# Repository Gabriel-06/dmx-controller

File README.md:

# DMX Controller
## The Boards 
### Board 2 Revision A
In revision A (REV A) the `S̅R̅C̅L̅R̅` pin on the shift register is pulled HIGH, this keeps the shift registers in a constantly cleared state. I thought that the issue was with the output enable pin (`O̅E̅`) as I said in my AT2, but this wasn’t the issue. I’m not even sure where that came from as the correction that I made to my board was on the right pin (`S̅R̅C̅L̅R̅`). In REV A, the NPN transistors to properly drive the 7-segment display are also missing. In order to use this revision, 2 cuts must be made as shown to cut the `S̅R̅C̅L̅R̅` pin from the ground plane. A wire can then be soldered directly onto the pin of the shift register that goes to an exposed +5V source. 2 possibilities for this are shown on the image below. In this revision the ICSP header is also flipped so the connector pinout is only correct on the back of the board, even though the silkscreen shows that the connector should be on the front. This is fixed in later revisions (I think). In this revision, for it to be bus powered (powered from USB) a wire needs to be soldered in from the fuse of the USB to the +5V port on the other side of the board (also in the image below, the white wire). Solder to the side after the fuse, as then it still gives you the protection. 

### Board 2 Revision B
In revision B (REV B), the same mistake exists regarding the `S̅R̅C̅L̅R̅` pin, except this time the output enable pin is wrongly pulled HIGH as well. 1 step forward, 2 steps back. So, for the revision B board, 3 points need to be cut, as outlined in the image below. Cut 1 is to cut the +5V rail going to the `O̅E̅` pin on the shift register. Cuts 2 and 3 are both to cut the `S̅R̅C̅L̅R̅` pin from the ground plane. This cut leaves you with a small floating ground plane island, but it shouldn’t really matter, there isn’t anything that sensitive around it. For all 3 cuts, you can simply use a small X-Acto knife or Stanley knife to cut the trace, similar to how you might on a strip board. 2 wires then have to be soldered directly onto the pins of the shift register going to an exposed +5V and GND point. I recommend using the exposed power input/output, as that isn’t used at all in the current design.

### Board 2 Revision C
Revision C (REV C) should have hopefully fixed all the issues, although I’m not going to order them, I’m happy just to keep the wires there. The files for it are in the GitHub if you would like to produce your own batch. No guarantees though….

### Board 1 Revision A
Similar to board 2, in revision A (REV A) of this board, the `S̅R̅C̅L̅R̅` pin on the shift registers are pulled HIGH, this keeps the shift registers in a constantly cleared state. 2 cuts need to make in the positions shown on the image below. A wire then has to be soldered directly onto the pin of the shift register and connected to a +5V source. The most convenient for me was the interconnect’s +5V line, as shown in the image below. 

### Board 1 Revision B
Revision B (REV B) should hopefully have fixed the issue. I’m not going to order any boards of this revision, but the files for it are in the GitHub, if you need to order anymore, or need it for reference.

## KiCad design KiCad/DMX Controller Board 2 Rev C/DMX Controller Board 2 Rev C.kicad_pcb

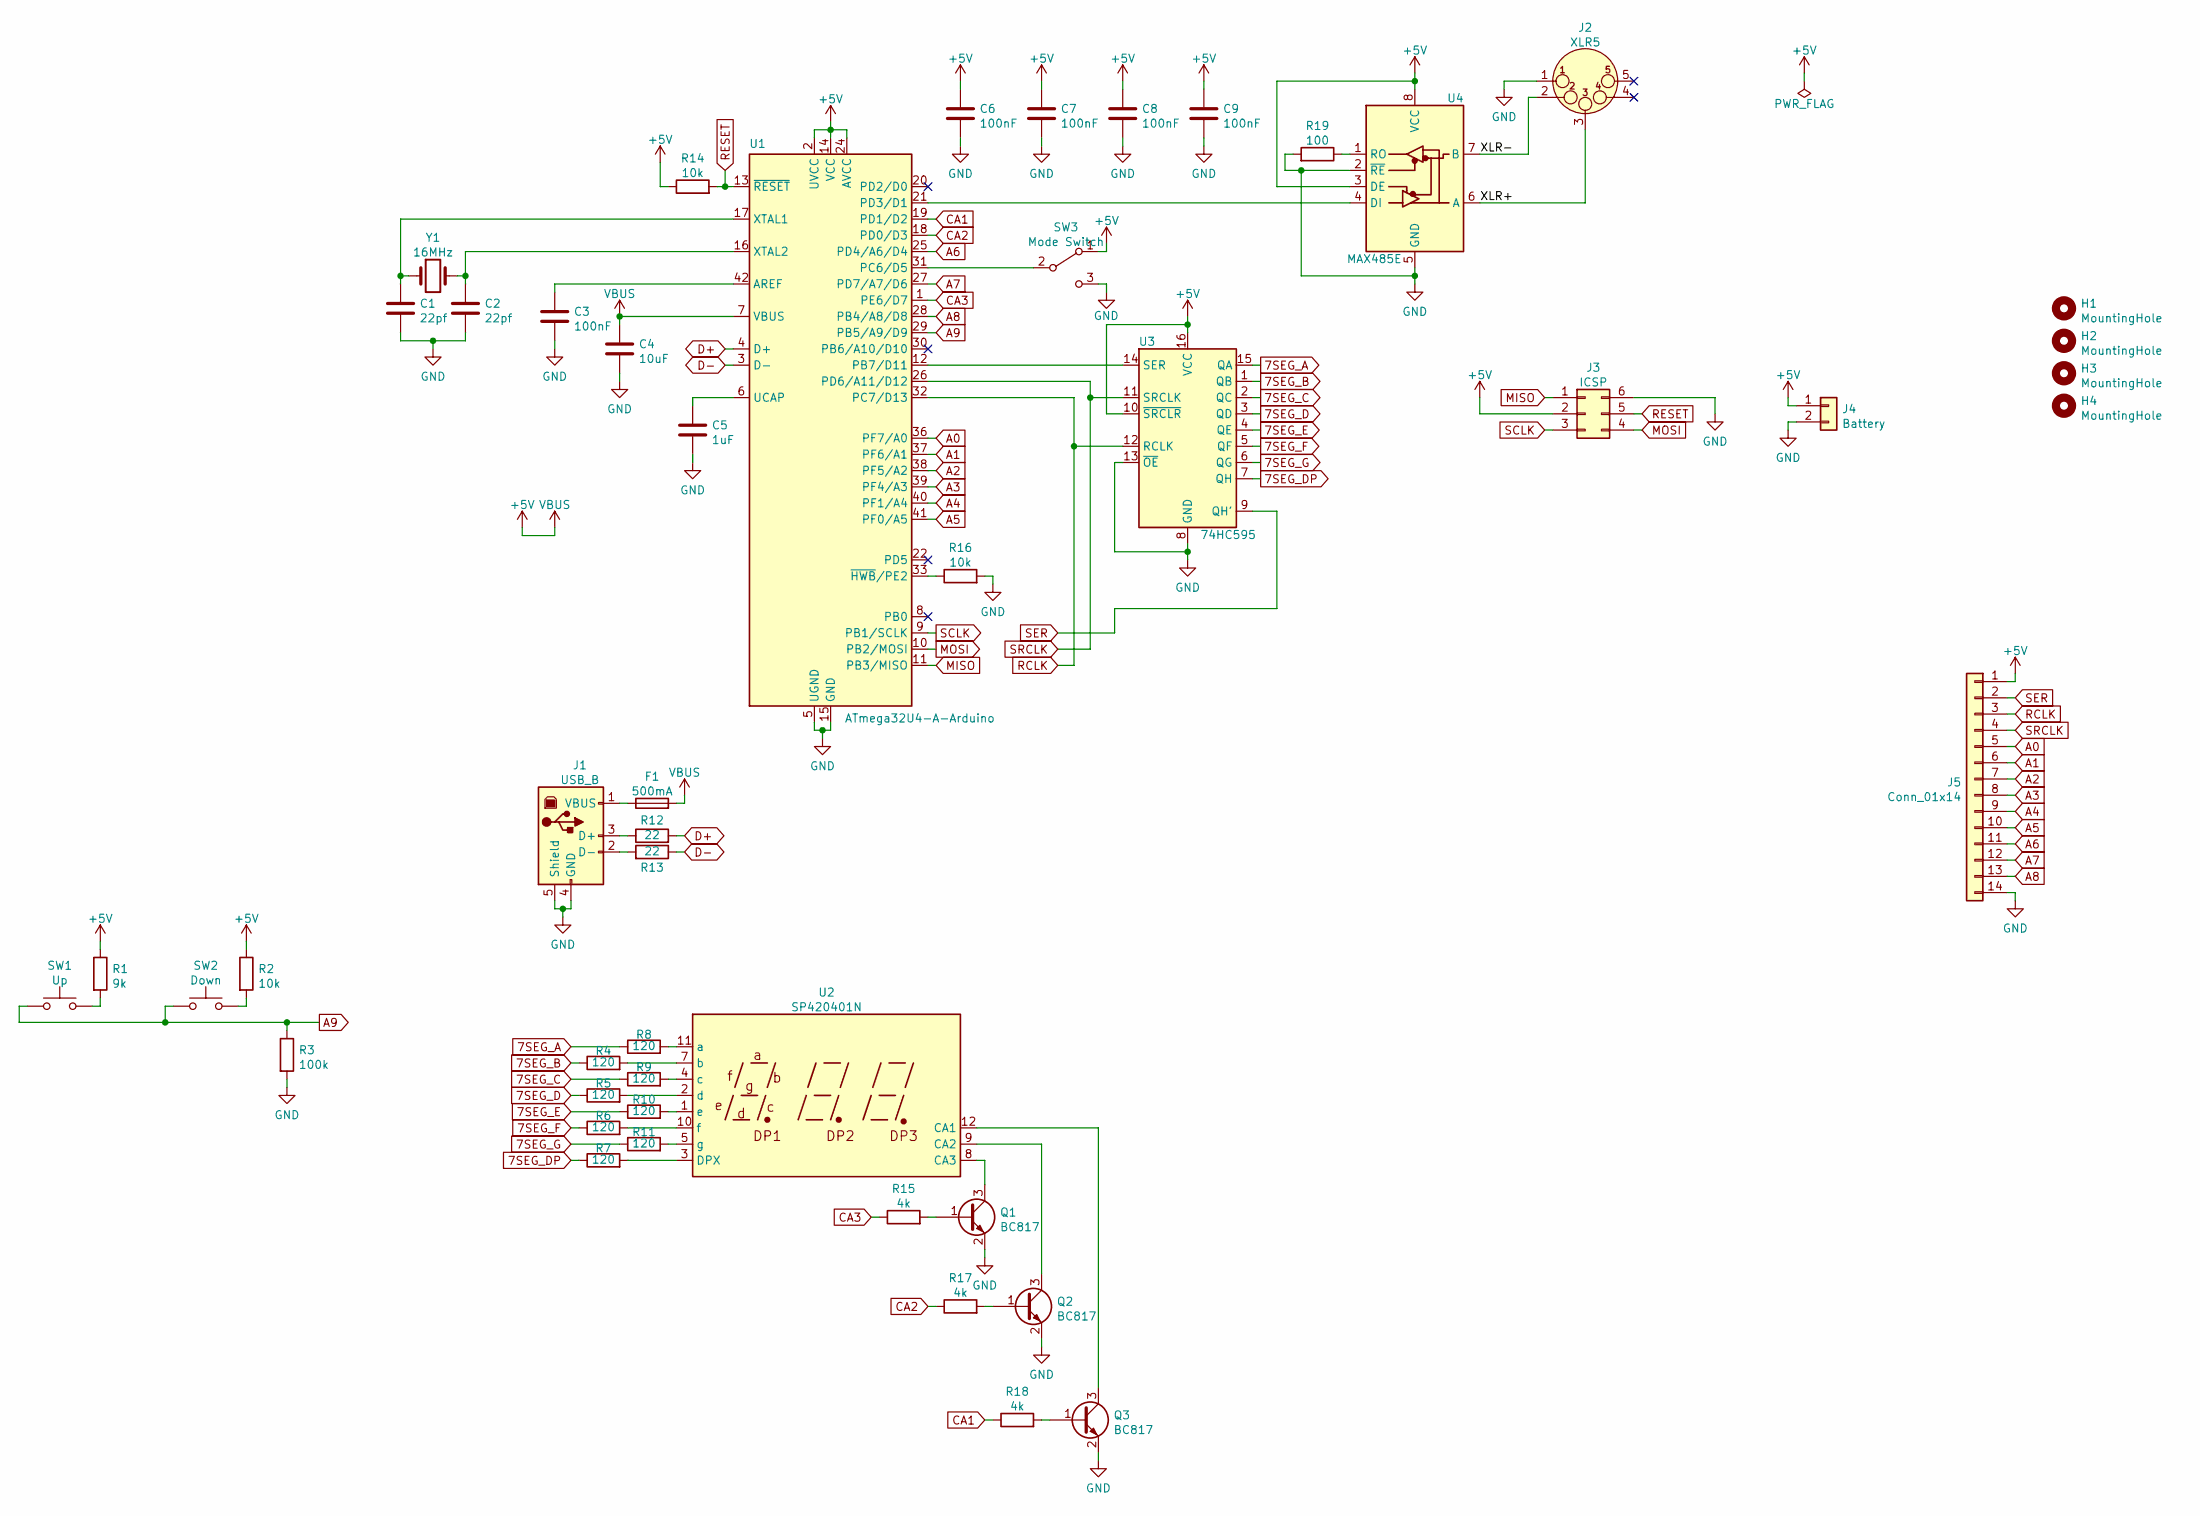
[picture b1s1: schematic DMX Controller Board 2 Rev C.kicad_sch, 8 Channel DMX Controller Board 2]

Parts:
C1, C2: 22pf; C_0805_2012Metric_Pad1.18x1.45mm_HandSolder
C3, C6, C7, C8, C9: 100nF; C_0805_2012Metric_Pad1.18x1.45mm_HandSolder
C4: 10uF; C_0805_2012Metric_Pad1.18x1.45mm_HandSolder
C5: 1uF; C_0805_2012Metric_Pad1.18x1.45mm_HandSolder
F1: 500mA; Fuse_1206_3216Metric_Pad1.42x1.75mm_HandSolder
H1, H2, H3, H4: MountingHole; MountingHole_3.2mm_M3
J1: USB_B; USB_B_USB-B02
J2: XLR5; PinHeader_1x03_P2.54mm_Vertical
J3: ICSP; PinSocket_2x03_P2.54mm_Vertical
J4: Battery; PinSocket_1x02_P2.54mm_Vertical
J5: Conn_01x14; PinSocket_1x14_P2.54mm_Vertical
Q1, Q2, Q3: BC817; SOT-23
R1: 9k; R_0805_2012Metric_Pad1.20x1.40mm_HandSolder
R2, R14, R16: 10k; R_0805_2012Metric_Pad1.20x1.40mm_HandSolder
R3: 100k; R_0805_2012Metric_Pad1.20x1.40mm_HandSolder
R4, R5, R6, R7, R8, R9, R10, R11: 120; R_0805_2012Metric_Pad1.20x1.40mm_HandSolder
R12, R13: 22; R_0805_2012Metric_Pad1.20x1.40mm_HandSolder
R15, R17, R18: 4k; R_0805_2012Metric_Pad1.20x1.40mm_HandSolder
R19: 100; R_0805_2012Metric_Pad1.20x1.40mm_HandSolder
SW1: Up; SW_PUSH_6mm_H13mm
SW2: Down; SW_PUSH_6mm_H13mm
SW3: Mode Switch; PinHeader_1x03_P2.54mm_Vertical
U1: ATmega32U4-A-Arduino; TQFP-44_10x10mm_P0.8mm
U2: SP420401N
U3: 74HC595; SOP-16_3.9x9.9mm_P1.27mm
U4: MAX485E; SOP-8_3.9x4.9mm_P1.27mm
Y1: 16MHz; Crystal_HC49-4H_Vertical

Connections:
7SEG_A: R8.1, U3.15 (QA)
7SEG_B: R4.1, U3.1 (QB)
7SEG_C: R9.1, U3.2 (QC)
7SEG_D: R5.1, U3.3 (QD)
7SEG_DP: R7.1, U3.7 (QH)
7SEG_E: R10.1, U3.4 (QE)
7SEG_F: R6.1, U3.5 (QF)
7SEG_G: R11.1, U3.6 (QG)
+5V: C4.1, C6.1, C7.1, C8.1, C9.1, F1.2, J3.2, J4.1, J5.1, R1.1, R2.1, R14.1, SW3.1 (A), U1.2 (UVCC), U1.7 (VBUS), U1.14 (VCC), U1.24 (AVCC), U1.34 (VCC), U1.44 (AVCC), U3.10 (~SRCLR), U3.16 (VCC), U4.3 (DE), U4.8 (VCC)
/XLR+: J2.3, U4.6 (A)
/XLR-: J2.2, U4.7 (B)
A0: J5.5, U1.36 (PF7/A0)
A1: J5.6, U1.37 (PF6/A1)
A2: J5.7, U1.38 (PF5/A2)
A3: J5.8, U1.39 (PF4/A3)
A4: J5.9, U1.40 (PF1/A4)
A5: J5.10, U1.41 (PF0/A5)
A6: J5.11, U1.25 (PD4/A6/D4)
A7: J5.12, U1.27 (PD7/A7/D6)
A8: J5.13, U1.28 (PB4/A8/D8)
A9: R3.1, SW1.1, SW2.1, U1.29 (PB5/A9/D9)
CA1: R18.1, U1.19 (PD1/D2)
CA2: R17.1, U1.18 (PD0/D3)
CA3: R15.1, U1.1 (PE6/D7)
D+: R12.2, U1.4 (D+)
D-: R13.1, U1.3 (D-)
GND: C1.2, C2.2, C3.2, C4.2, C5.2, C6.2, C7.2, C8.2, C9.2, J1.4 (GND), J1.5 (Shield), J2.1, J3.6, J4.2, J5.14, Q1.2 (E), Q2.2 (E), Q3.2 (E), R3.2, R16.2, R19.2, SW3.3 (C), U1.5 (UGND), U1.15 (GND), U1.23 (GND), U1.35 (GND), U1.43 (GND), U3.8 (GND), U3.13 (~OE), U4.2 (~RE), U4.5 (GND)
MISO: J3.1, U1.11 (PB3/MISO)
MOSI: J3.4, U1.10 (PB2/MOSI)
unnamed: C1.1, U1.17 (XTAL1), Y1.1
unnamed: C2.1, U1.16 (XTAL2), Y1.2
unnamed: C3.1, U1.42 (AREF)
unnamed: C5.1, U1.6 (UCAP)
unnamed: F1.1, J1.1 (VBUS)
unnamed: J1.2 (D-), R13.2
unnamed: J1.3 (D+), R12.1
unnamed: Q1.1 (B), R15.2
unnamed: Q1.3 (C), U2.8 (CA3)
unnamed: Q2.1 (B), R17.2
unnamed: Q2.3 (C), U2.9 (CA2)
unnamed: Q3.1 (B), R18.2
unnamed: Q3.3 (C), U2.12 (CA1)
unnamed: R1.2, SW1.2
unnamed: R2.2, SW2.2
unnamed: R4.2, U2.7 (b)
unnamed: R5.2, U2.2 (d)
unnamed: R6.2, U2.10 (f)
unnamed: R7.2, U2.3 (DPX)
unnamed: R8.2, U2.11 (a)
unnamed: R9.2, U2.4 (c)
unnamed: R10.2, U2.1 (e)
unnamed: R11.2, U2.5 (g)
unnamed: R16.1, U1.33 (~HWB~/PE2)
unnamed: R19.1, U4.1 (RO)
unnamed: SW3.2 (B), U1.31 (PC6/D5)
unnamed: U1.12 (PB7/D11), U3.14 (SER)
unnamed: U1.21 (PD3/D1), U4.4 (DI)
RCLK: J5.3, U1.32 (PC7/D13), U3.12 (RCLK)
RESET: J3.5, R14.2, U1.13 (~RESET)
SCLK: J3.3, U1.9 (PB1/SCLK)
SER: J5.2, U3.9 (QH')
SRCLK: J5.4, U1.26 (PD6/A11/D12), U3.11 (SRCLK)

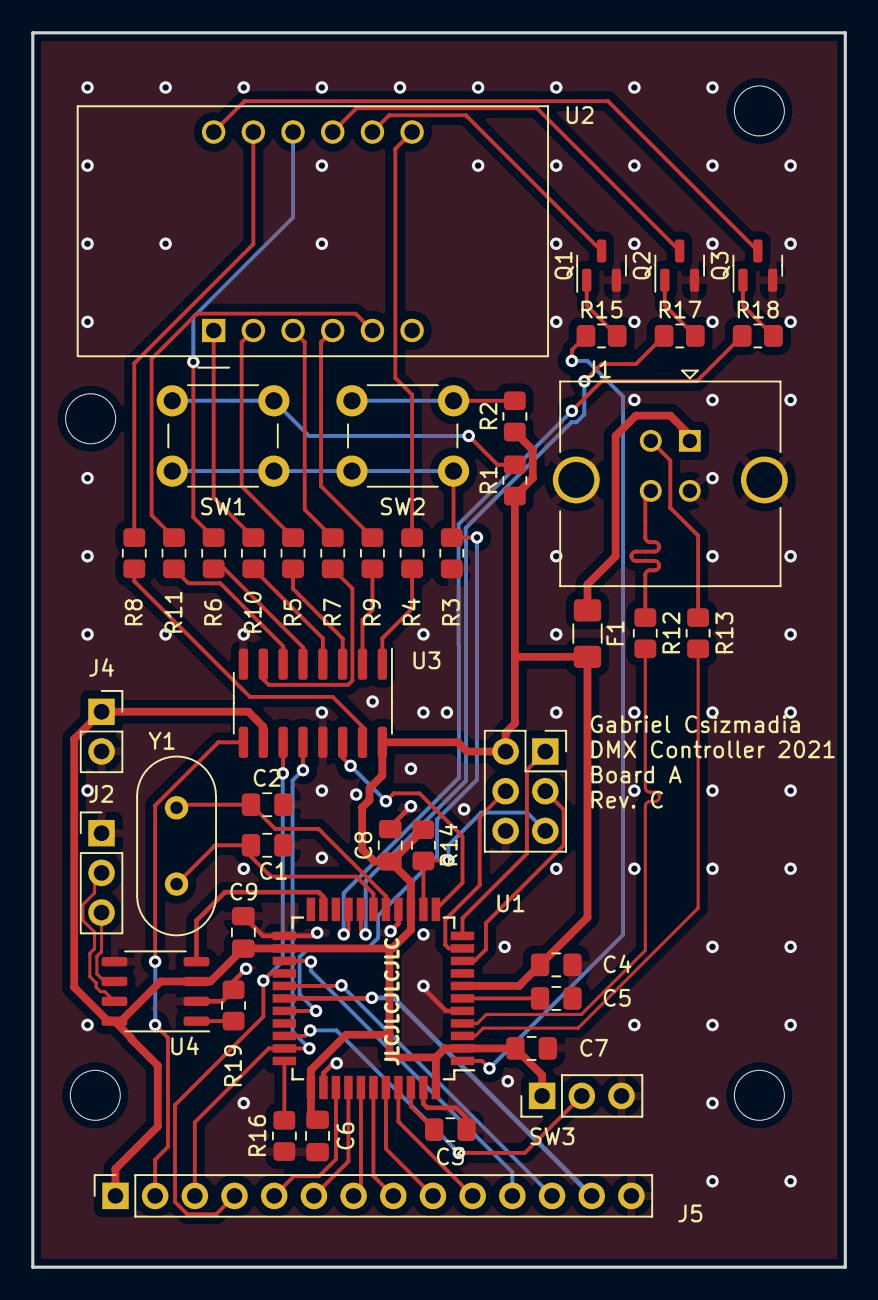
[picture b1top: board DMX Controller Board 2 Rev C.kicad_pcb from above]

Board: 2 copper layers, 52.0 x 79.0 mm, 49 parts (0 on the bottom side), 62 nets.

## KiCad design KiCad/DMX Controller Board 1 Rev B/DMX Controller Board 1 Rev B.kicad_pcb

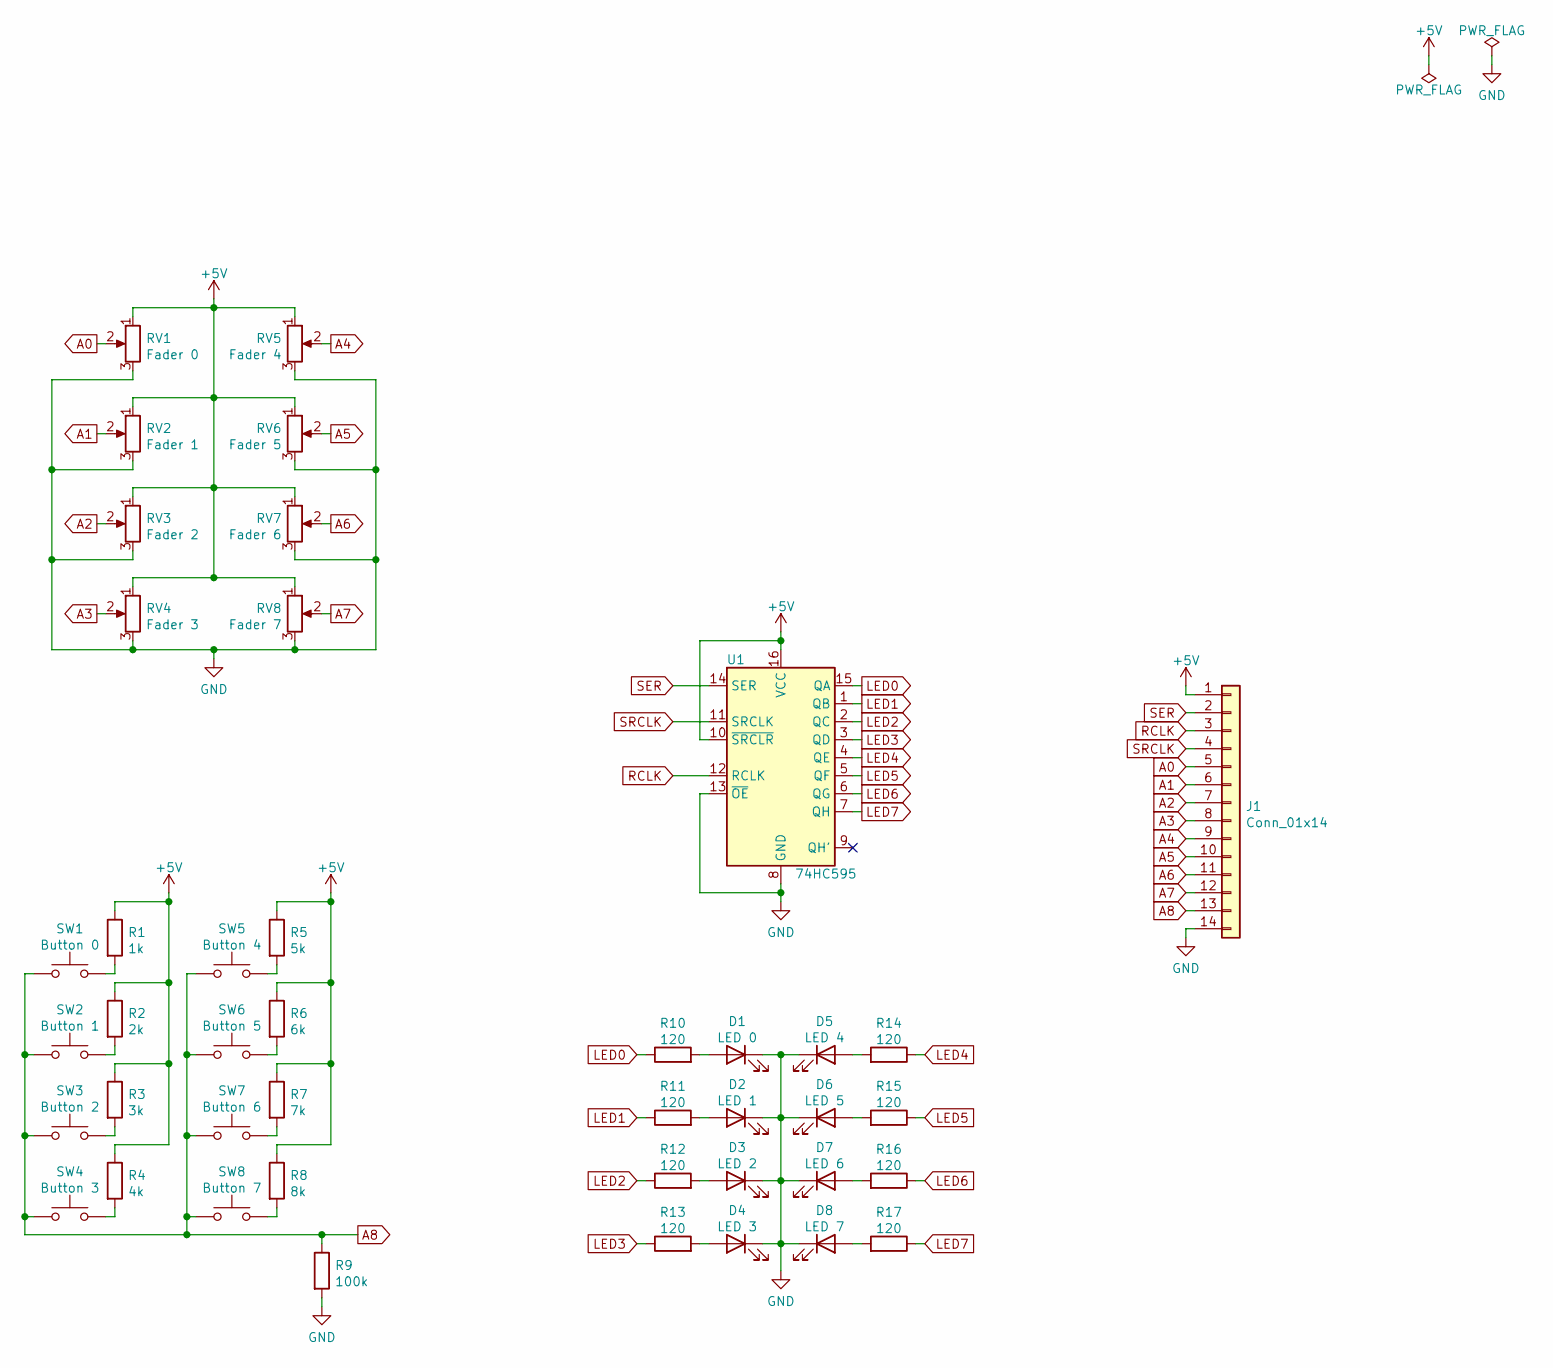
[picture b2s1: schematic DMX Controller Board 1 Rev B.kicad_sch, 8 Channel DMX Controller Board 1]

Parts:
D1: LED 0; LED_D3.0mm
D2: LED 1; LED_D3.0mm
D3: LED 2; LED_D3.0mm
D4: LED 3; LED_D3.0mm
D5: LED 4; LED_D3.0mm
D6: LED 5; LED_D3.0mm
D7: LED 6; LED_D3.0mm
D8: LED 7; LED_D3.0mm
J1: Conn_01x14; PinSocket_1x14_P2.54mm_Vertical
R1: 1k; R_0805_2012Metric_Pad1.20x1.40mm_HandSolder
R2: 2k; R_0805_2012Metric_Pad1.20x1.40mm_HandSolder
R3: 3k; R_0805_2012Metric_Pad1.20x1.40mm_HandSolder
R4: 4k; R_0805_2012Metric_Pad1.20x1.40mm_HandSolder
R5: 5k; R_0805_2012Metric_Pad1.20x1.40mm_HandSolder
R6: 6k; R_0805_2012Metric_Pad1.20x1.40mm_HandSolder
R7: 7k; R_0805_2012Metric_Pad1.20x1.40mm_HandSolder
R8: 8k; R_0805_2012Metric_Pad1.20x1.40mm_HandSolder
R9: 100k; R_0805_2012Metric_Pad1.20x1.40mm_HandSolder
R10, R11, R12, R13, R14, R15, R16, R17: 120; R_0805_2012Metric_Pad1.20x1.40mm_HandSolder
RV1: Fader 0; Potentiometer_Alps_RS6011SP
RV2: Fader 1; Potentiometer_Alps_RS6011SP
RV3: Fader 2; Potentiometer_Alps_RS6011SP
RV4: Fader 3; Potentiometer_Alps_RS6011SP
RV5: Fader 4; Potentiometer_Alps_RS6011SP
RV6: Fader 5; Potentiometer_Alps_RS6011SP
RV7: Fader 6; Potentiometer_Alps_RS6011SP
RV8: Fader 7; Potentiometer_Alps_RS6011SP
SW1: Button 0; SW_PUSH_6mm_H13mm
SW2: Button 1; SW_PUSH_6mm_H13mm
SW3: Button 2; SW_PUSH_6mm_H13mm
SW4: Button 3; SW_PUSH_6mm_H13mm
SW5: Button 4; SW_PUSH_6mm_H13mm
SW6: Button 5; SW_PUSH_6mm_H13mm
SW7: Button 6; SW_PUSH_6mm_H13mm
SW8: Button 7; SW_PUSH_6mm_H13mm
U1: 74HC595; SOP-16_3.9x9.9mm_P1.27mm

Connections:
+5V: J1.1, R1.1, R2.1, R3.1, R4.1, R5.1, R6.1, R7.1, R8.1, RV1.1, RV2.1, RV3.1, RV4.1, RV5.1, RV6.1, RV7.1, RV8.1, U1.10 (~SRCLR), U1.16 (VCC)
A0: J1.5, RV1.2
A1: J1.6, RV2.2
A2: J1.7, RV3.2
A3: J1.8, RV4.2
A4: J1.9, RV5.2
A5: J1.10, RV6.2
A6: J1.11, RV7.2
A7: J1.12, RV8.2
A8: J1.13, R9.1, SW1.1, SW2.1, SW3.1, SW4.1, SW5.1, SW6.1, SW7.1, SW8.1
GND: D1.1 (K), D2.1 (K), D3.1 (K), D4.1 (K), D5.1 (K), D6.1 (K), D7.1 (K), D8.1 (K), J1.14, R9.2, RV1.3, RV2.3, RV3.3, RV4.3, RV5.3, RV6.3, RV7.3, RV8.3, U1.8 (GND), U1.13 (~OE)
LED0: R10.1, U1.15 (QA)
LED1: R11.1, U1.1 (QB)
LED2: R12.1, U1.2 (QC)
LED3: R13.1, U1.3 (QD)
LED4: R14.1, U1.4 (QE)
LED5: R15.1, U1.5 (QF)
LED6: R16.1, U1.6 (QG)
LED7: R17.1, U1.7 (QH)
unnamed: D1.2 (A), R10.2
unnamed: D2.2 (A), R11.2
unnamed: D3.2 (A), R12.2
unnamed: D4.2 (A), R13.2
unnamed: D5.2 (A), R14.2
unnamed: D6.2 (A), R15.2
unnamed: D7.2 (A), R16.2
unnamed: D8.2 (A), R17.2
unnamed: R1.2, SW1.2
unnamed: R2.2, SW2.2
unnamed: R3.2, SW3.2
unnamed: R4.2, SW4.2
unnamed: R5.2, SW5.2
unnamed: R6.2, SW6.2
unnamed: R7.2, SW7.2
unnamed: R8.2, SW8.2
RCLK: J1.3, U1.12 (RCLK)
SER: J1.2, U1.14 (SER)
SRCLK: J1.4, U1.11 (SRCLK)

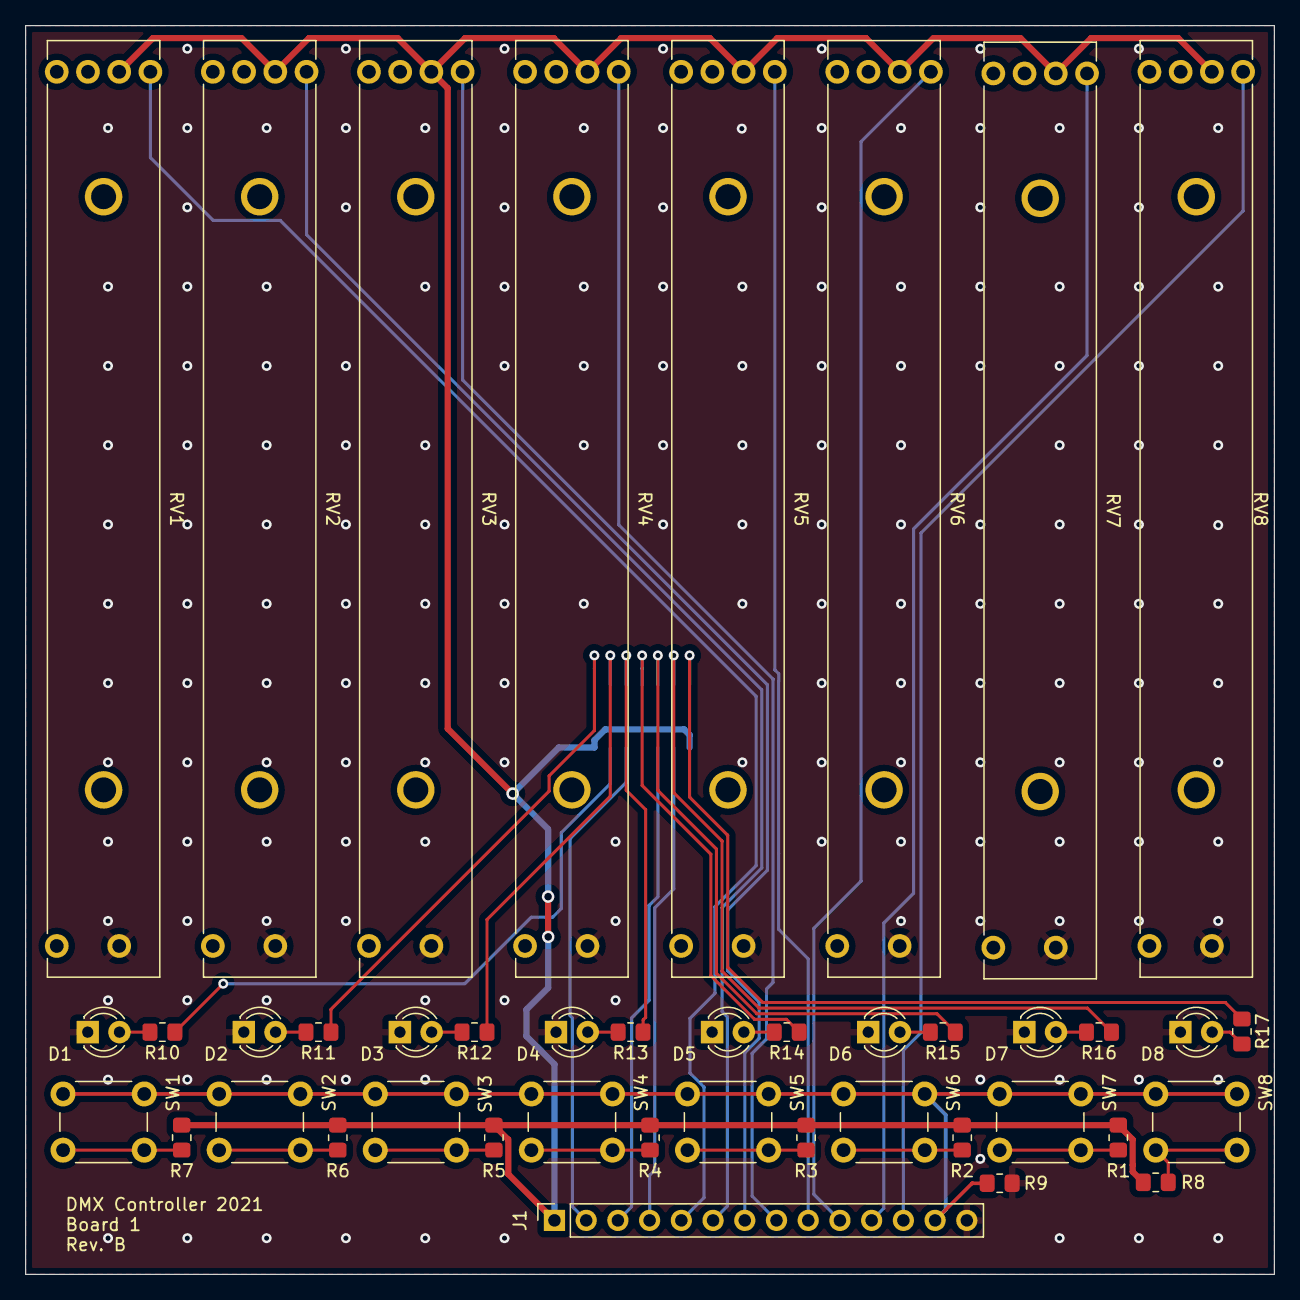
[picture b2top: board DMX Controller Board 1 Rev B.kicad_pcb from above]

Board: 2 copper layers, 100.0 x 100.0 mm, 43 parts (1 on the bottom side), 38 nets.

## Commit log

2021-11-11 Added KiCad files along with code and case
2022-01-18 idek

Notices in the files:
KiCad/DMX Controller Board 1 Rev B/DMX Controller Board 1 Rev B.kicad_pcb:
Copyright 2021 Gabriel Csizmadia
